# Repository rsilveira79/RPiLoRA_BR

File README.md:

# RPiLoRA_BR

Raspberry Pi shield for LoRa
- RFM96
- 433 MHz

ADC Converter (IC2-based)
- ADS1015

Humidity and temperature sensing
- HIH6131

Luminosity sensing
- TSL2561

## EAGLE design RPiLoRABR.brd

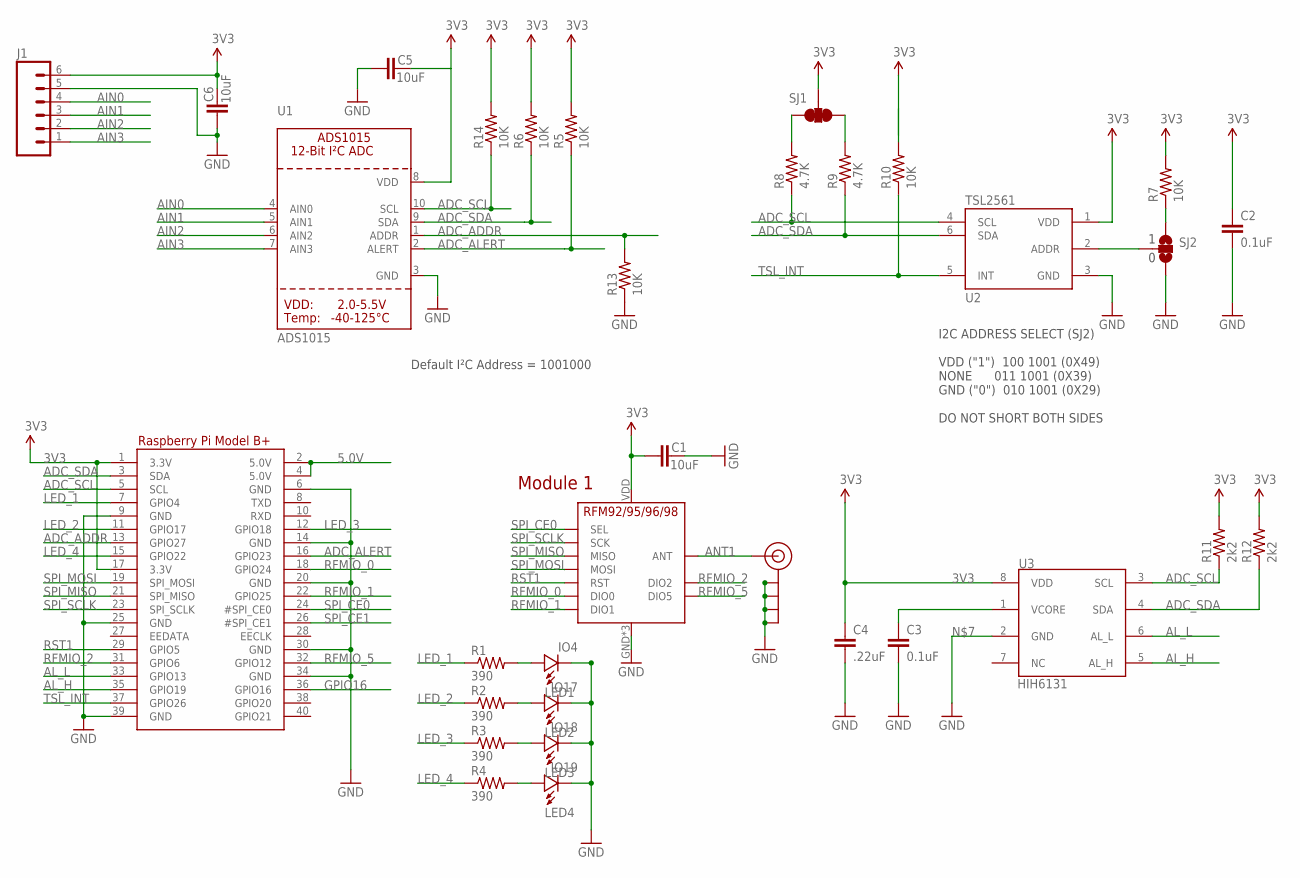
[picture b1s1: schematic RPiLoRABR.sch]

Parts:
ANT: ANTENNATINY; SMA_UFL_PAD_TINY
C1, C5, C6: 10uF; 0805-CAP
C2, C3: 0.1uF; 0603-CAP
C4: .22uF; 0603-CAP
J1: M06LOCK_LONGPADS; 1X06_LOCK_LONGPADS
LED1: IO4; 0805-LED
LED2: IO17; 0805-LED
LED3: IO18; 0805-LED
LED4: IO19; 0805-LED
R1, R2, R3, R4: 390; 0805-RES
R5, R6, R7, R10, R13, R14: 10K; 0603-RES@1
R8, R9: 4.7K; 0603-RES@1
R11, R12: 2k2; 0603-RES@1
RPI1: RASPBERRYPI_BPLUS_HATNOSLOTS; PI_HAT_NOSLOTS
SJ1: SOLDERJUMPER_2WAYPASTE1&2&3; SJ_3_PASTE1&2&3
SJ2: SOLDERJUMPER_2WAYS; SJ_3
U1: ADS1015; MSOP10
U2: TSL2561; FN-6
U3: HIH6131; SOIC8
U4: RFM95

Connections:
3V3: C1.1, C2.1, C4.1, C5.2, C6.2, J1.6, R5.2, R6.2, R7.2, R10.2, R11.2, R12.2, R14.2, RPI1.1 (3.3V), RPI1.17 (3.3V), SJ1.2, U1.8 (VDD), U2.1 (VDD), U3.8 (VDD), U4.VDD (VCC)
5.0V: RPI1.2 (5.0V), RPI1.4 (5.0V)
ADC_ADDR: R13.2, RPI1.13 (GPIO27), U1.1 (ADDR)
ADC_ALERT: R5.1, RPI1.16 (GPIO23), U1.2 (ALERT)
ADC_SCL: R8.1, R11.1, R14.1, RPI1.5 (SCL), U1.10 (SCL), U2.4 (SCL), U3.3 (SCL)
ADC_SDA: R6.1, R9.1, R12.1, RPI1.3 (SDA), U1.9 (SDA), U2.6 (SDA), U3.4 (SDA)
AIN0: J1.4, U1.4 (AIN0)
AIN1: J1.3, U1.5 (AIN1)
AIN2: J1.2, U1.6 (AIN2)
AIN3: J1.1, U1.7 (AIN3)
AL_H: RPI1.35 (GPIO19), U3.5 (AL_H)
AL_L: RPI1.33 (GPIO13), U3.6 (AL_L)
ANT1: ANT.ANT1 (SIGNAL), ANT.ANT2 (SIGNAL), ANT.ANT3 (SIGNAL), U4.ANT
GND: ANT.GND1 (GND), ANT.GND2 (GND), ANT.GND3 (GND), ANT.GND4 (GND), C1.2, C2.2, C3.2, C4.2, C5.1, C6.1, J1.5, LED1.MINUS, LED2.MINUS, LED3.MINUS, LED4.MINUS, R13.1, RPI1.6 (GND), RPI1.9 (GND), RPI1.14 (GND), RPI1.20 (GND), RPI1.25 (GND), RPI1.30 (GND), RPI1.34 (GND), RPI1.39 (GND), SJ2.3, U1.3 (GND), U2.3 (GND), U4.GND, U4.GND1 (GND), U4.GND2 (GND)
GPIO16: RPI1.36 (GPIO16)
LED_1: R1.1, RPI1.7 (GPIO4)
LED_2: R2.1, RPI1.11 (GPIO17)
LED_3: R3.1, RPI1.12 (GPIO18)
LED_4: R4.1, RPI1.15 (GPIO22)
unnamed: R7.1, SJ2.1
unnamed: SJ2.2, U2.2 (ADDR)
unnamed: C3.1, U3.1 (VCORE)
unnamed: R9.2, SJ1.1
unnamed: R8.2, SJ1.3
unnamed: LED4.PLUS, R4.2
unnamed: LED1.PLUS, R1.2
unnamed: LED2.PLUS, R2.2
unnamed: LED3.PLUS, R3.2
RFMIO_0: RPI1.18 (GPIO24), U4.DIO0
RFMIO_1: RPI1.22 (GPIO25), U4.DIO1
RFMIO_2: RPI1.31 (GPIO6), U4.DIO2
RFMIO_5: RPI1.32 (GPIO12), U4.DIO5
RST1: RPI1.29 (GPIO5), U4.RST
SPI_CE0: RPI1.24 (#SPI_CE0), U4.NSS (SEL)
SPI_CE1: RPI1.26 (#SPI_CE1)
SPI_MISO: RPI1.21 (SPI_MISO), U4.MISO
SPI_MOSI: RPI1.19 (SPI_MOSI), U4.MOSI
SPI_SCLK: RPI1.23 (SPI_SCLK), U4.SCK
TSL_INT: R10.1, RPI1.37 (GPIO26), U2.5 (INT)

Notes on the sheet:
Module 1
I2C ADDRESS SELECT (SJ2) VDD ("1") 100 1001 (0X49) NONE 011 1001 (0X39) GND ("0") 010 1001 (0X29) DO NOT SHORT BOTH SIDES
Default I²C Address = 1001000

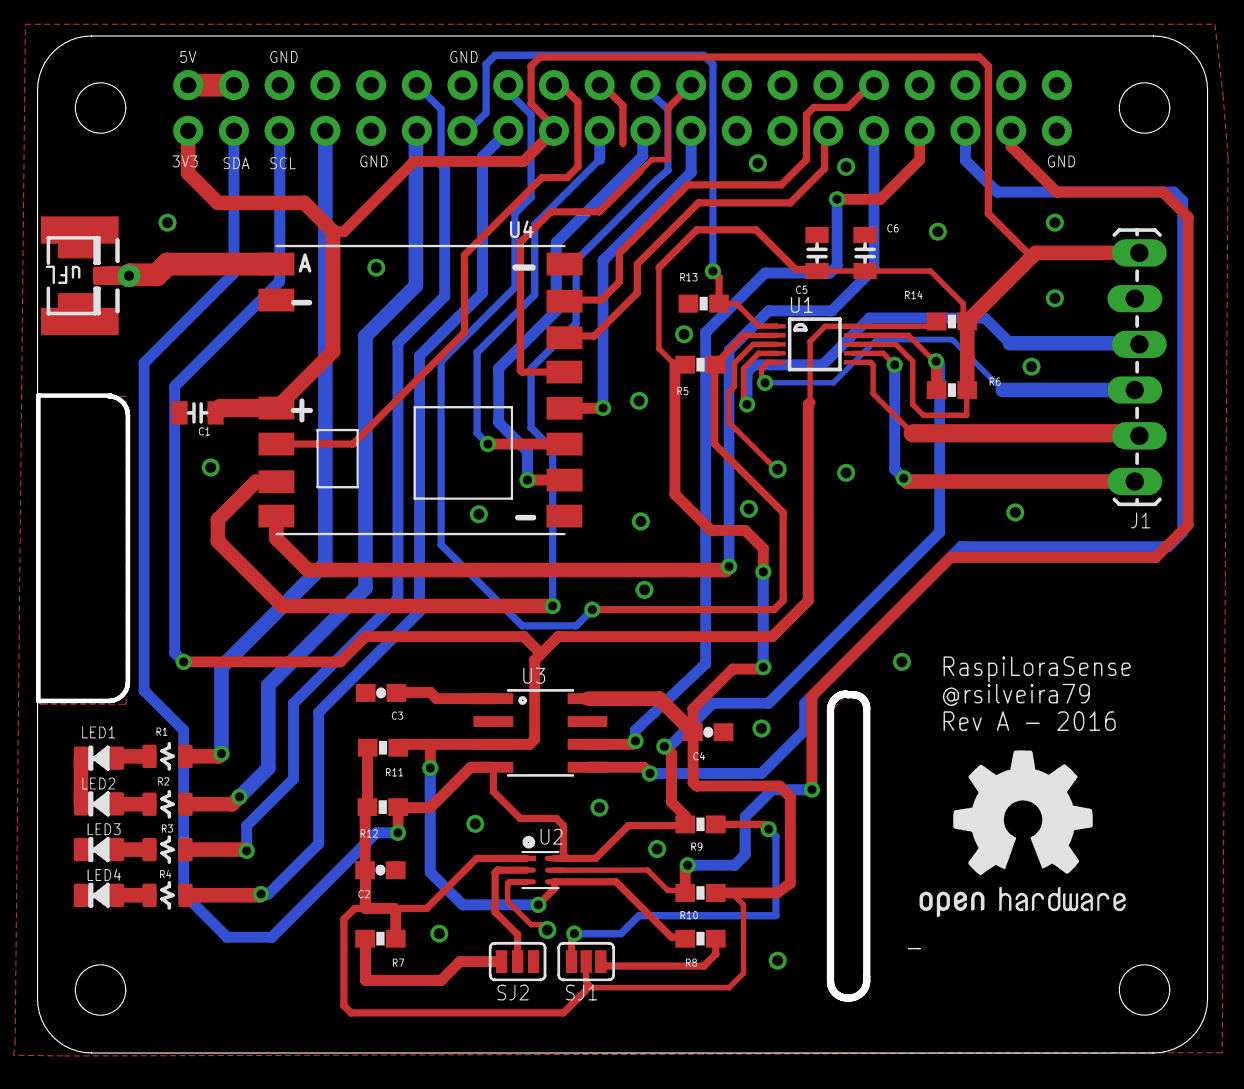
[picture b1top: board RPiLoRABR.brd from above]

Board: 2 copper layers, 65.0 x 56.5 mm, 35 parts (0 on the bottom side), 37 nets.

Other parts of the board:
U$1: OSHW1
U$2: A4L-LOC

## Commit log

2016-08-27 Primeiro esquematico
2016-08-28 Final board - Rev A, with BRD, SCH and PDF
2016-08-30 Board modified, final Gerbers sent to OSHPark including board outline update, top silk positions and PCB slot holes
2017-03-24 Set theme jekyll-theme-time-machine

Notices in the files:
parts and their libraries:
microbuilder: This work is placed in the public domain, and may be freely used for commercial and non-commercial work with the following conditions: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
SparkFun-Resistors: Licensing: CC v3.0 Share-Alike You are welcome to use this library for commercial purposes.
